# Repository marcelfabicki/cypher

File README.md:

<p align="center"><sub><i>Assembled Prototype v0.1.0</i></sub></p>

<h1 style="text-align:center;">CYPHER</h1>

**CYPHER** is an open-source, autonomous two-wheeled bipedal AI robot. Being a wheeled-legged robot, powered by a Raspberry Pi 5 and equipped with a camera and distance sensor, Cypher can navigate around obstacles and maintain balance on uneven surfaces, but most notably, through OpenAI's Realtime API and inspired by the personality of Tars (Interstellar), Cypher can talk, ask questions, and act on commands (with its own unique personality and humour).

## Project Status & Next Steps

The robot has been fully designed, printed and assembled. All hardware required for self-balancing and movement including servos, wheel BLDC motors and encoders, buck converters, and ultrasonic distance sensor have been installed and connected to the PCB so the next stage is to begin coding leg-movement and self-balancing firmware on the ESP32.

Some modifications had to be made to the PCB. These included soldering wires to the underside corresponding to pins 5, 15, 21, and 22 of the ESP32 to allow for I2C communication with the AS5600 magnetic encoders - originally PCB routed to PWM input pins which unfortunately proved unreliable. In addition 2.2k pull-up resisters were soldered to pins 5 and 15 to stabilise the I2C line. In v1 the PCB files ([hardware/pcb/](hardware/pcb/)) will be re-routed according to any modification.

The current design (available inside [hardware/cad](hardware/cad/)) includes approximately 45 3d-printed parts and over 130 screws to assemble. The BOM, full assembly instructions and documentation will be available with v1. 

## Hardware Overview
- **Battery:** 11.1V 3S 2200mAh LiPo
- **PCB:** 2 layer custom PCB for power distribution & signal routing
- **Compute:** ESP32 + Raspberry Pi 5
- **Sensors:** AS5600 magnetic encoders, INA226 voltage sensor, MPU6050 IMU, INMP441 microphone, HCSR04 ultrasonic distance sensor
- **BLDC Driver:** SimpleFOCMini driver
- **Actuators:** MG996R + 20kg servos, 2208 80T brushless gimbal motors
- **Buck-Converters:** XL4016, 60W DFRobot Adjustable Buck Module

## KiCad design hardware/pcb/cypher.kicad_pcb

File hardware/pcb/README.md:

# PCB Hardware Status

## Rev 0.1 (Current - Requires Modification)
- Functional with manual modifications (soldering additional wires and pull-up resistors to the underside ESP32 pins)
- Gerbers will be included once changes for Rev 0.2 have been made

## Planned for Rev 0.2
- Re-route AS5600 magnetic encoder connector traces with ESP32
- Add 2.2k I2C pull-ups

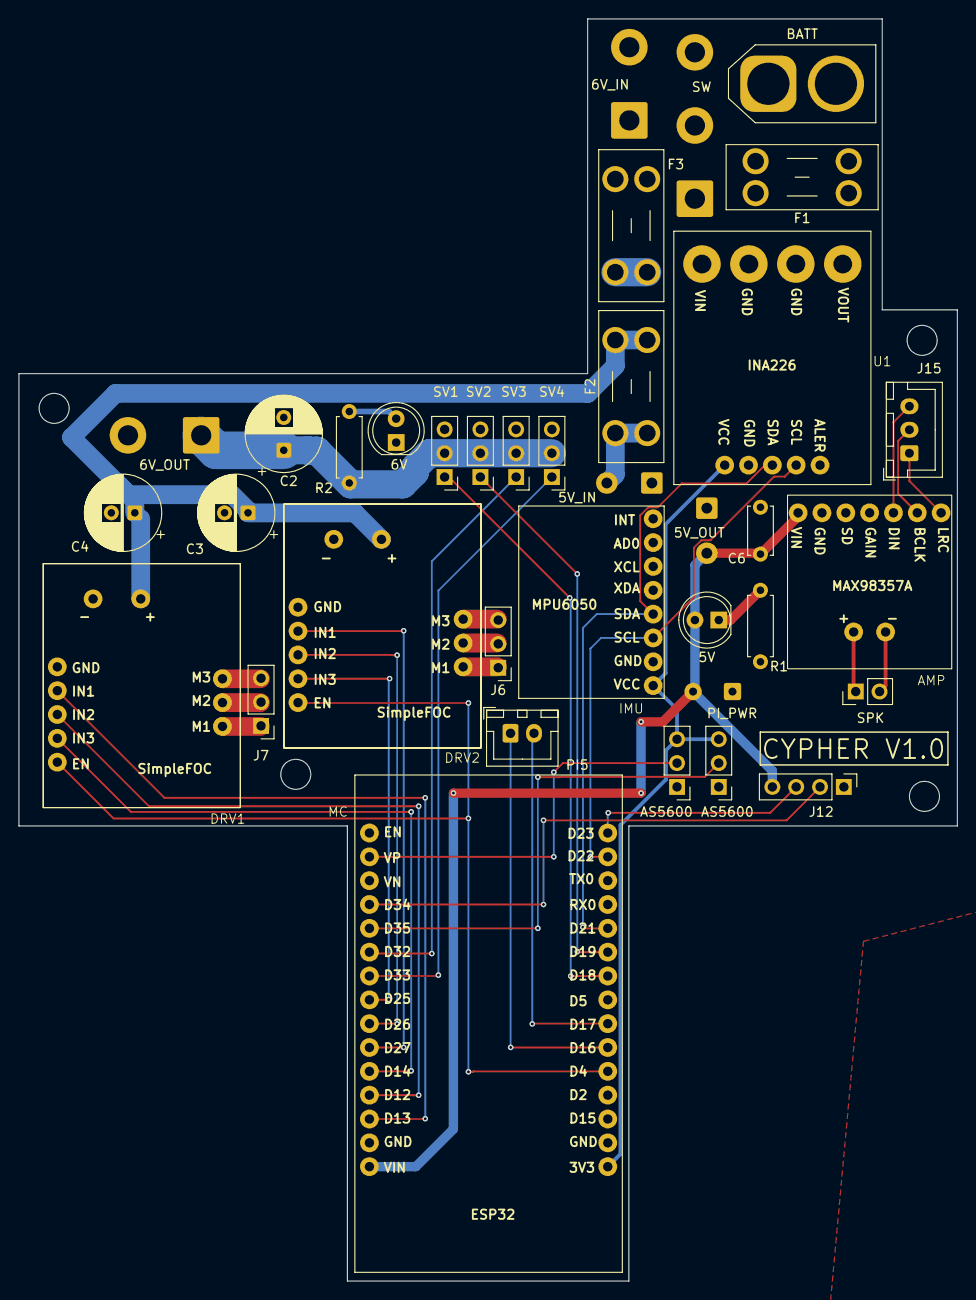
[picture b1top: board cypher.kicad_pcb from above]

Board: 2 copper layers, 100.0 x 134.5 mm, 36 parts (0 on the bottom side), 42 nets.

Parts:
5V, 6V: LED; LED_D5.0mm
5V_IN: UBEC IN; SolderWire-0.5sqmm_1x02_P4.8mm_D0.9mm_OD2.3mm
5V_OUT: UBEC OUT; SolderWire-0.5sqmm_1x02_P4.8mm_D0.9mm_OD2.3mm
6V_IN: XL4016 IN; SolderWire-1.5sqmm_1x02_P7.8mm_D1.7mm_OD3.9mm
6V_OUT: XL4016 OUT; SolderWire-1.5sqmm_1x02_P7.8mm_D1.7mm_OD3.9mm
AMP: MAX98357A Amplifer; MAX98357A Module
AS5600, AS5600#2: AS5600; PinHeader_1x03_P2.54mm_Vertical
BATT: BATT IN; AMASS_XT60-F_1x02_P7.20mm_Vertical
C2: C_Polarized; CP_Radial_D8.0mm_P3.50mm
C3, C4: C_Polarized; CP_Radial_D8.0mm_P2.50mm
C6: C; C_Disc_D5.0mm_W2.5mm_P5.00mm
DRV1, DRV2: SimpleFOC
F1, F2, F3: Fuse; Fuseholder_Blade_Mini_Keystone_3568
IMU: MPU6050 IMU; MPU6050 Module
J6, J7: Motor; PinHeader_1x03_P2.54mm_Vertical
J12: HCSRO4P; PinHeader_1x04_P2.54mm_Vertical
J15: PI Audio; JST_XH_B3B-XH-A_1x03_P2.50mm_Vertical
MC: ESP32; ESP32 Module
PI5: PI Communication; JST_XH_B2B-XH-A_1x02_P2.50mm_Vertical
PI_PWR: PI Power; SolderWire-0.25sqmm_1x02_P4.2mm_D0.65mm_OD1.7mm
R1, R2: 330; R_Axial_DIN0207_L6.3mm_D2.5mm_P7.62mm_Horizontal
SPK: Speaker; PinHeader_1x02_P2.54mm_Vertical
SV1: Servo4; PinHeader_1x03_P2.54mm_Vertical
SV2: Servo3; PinHeader_1x03_P2.54mm_Vertical
SV3: Servo2; PinHeader_1x03_P2.54mm_Vertical
SV4: Servo1; PinHeader_1x03_P2.54mm_Vertical
SW: Switch; SolderWire-1.5sqmm_1x03_P7.8mm_D1.7mm_OD3.9mm
U1: INA226; INA226 Module

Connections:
12V_SW: SW.1, U1.4 (VIN)
12V_SYS: C3.1, C4.1, DRV1.7 (+), DRV2.7 (+), F2.2, F3.1, U1.1 (VOUT)
+3V3: AS5600.3, AS5600#2.3, IMU.1 (VCC), MC.16 (3V3), U1.9 (VCC)
+5V: 5V.2 (A), 5V_OUT.2, AMP.9 (VIN), C6.2, J12.4, MC.1 (VIN), PI_PWR.2
+6V_DIRTY: 6V_OUT.1, C2.1, R2.1, SV1.2, SV2.2, SV3.2, SV4.2
+12V: BATT.2, F1.1
GND: 5V_IN.1, 5V_OUT.1, 6V.1 (K), 6V_IN.2, 6V_OUT.2, AMP.6 (GAIN), AMP.8 (GND), AS5600.1, AS5600#2.1, BATT.1, C2.2, C3.2, C4.2, C6.1, DRV1.1 (GND), DRV1.6 (-), DRV2.1 (GND), DRV2.6 (-), IMU.2 (GND), J12.1, MC.2 (GND), PI_PWR.1, R1.2, SV1.3, SV2.3, SV3.3, SV4.3, SW.3, U1.2 (GND), U1.3 (GND), U1.8 (GND)
unnamed: 5V.1 (K), R1.1
unnamed: 6V.2 (A), R2.2
unnamed: F1.2, SW.2
unnamed: 6V_IN.1, F3.2
unnamed: DRV2.10 (M1), J6.1
unnamed: DRV2.9 (M2), J6.2
unnamed: DRV2.8 (M3), J6.3
unnamed: DRV1.10 (M1), J7.1
unnamed: DRV1.9 (M2), J7.2
unnamed: DRV1.8 (M3), J7.3
unnamed: MC.9 (D33), SV4.1
unnamed: MC.10 (D32), SV3.1
unnamed: MC.25 (D19), SV2.1
unnamed: MC.24 (D18), SV1.1
unnamed: J12.2, MC.12 (D34)
unnamed: J12.3, MC.30 (D23)
unnamed: AMP.2 (+), SPK.1
unnamed: AMP.1 (-), SPK.2
unnamed: MC.21 (D16), PI5.1
unnamed: MC.22 (D17), PI5.2
unnamed: AMP.3 (LRC), J15.1
unnamed: AMP.4 (BCLK), J15.2
unnamed: AMP.5 (DIN), J15.3
unnamed: AS5600#2.2, MC.14 (VP)
unnamed: AS5600.2, MC.11 (D35)
unnamed: 5V_IN.2, F2.1
unnamed: IMU.3 (SCL), MC.29 (D22), U1.6 (SCL)
unnamed: IMU.4 (SDA), MC.26 (D21), U1.7 (SDA)
unnamed: DRV1.5 (EN), DRV2.5 (EN), MC.20 (D4)
unnamed: DRV2.2 (IN1), MC.6 (D27)
unnamed: DRV2.3 (IN2), MC.7 (D26)
unnamed: DRV2.4 (IN3), MC.8 (D25)
unnamed: DRV1.2 (IN1), MC.3 (D13)
unnamed: DRV1.3 (IN2), MC.4 (D12)
unnamed: DRV1.4 (IN3), MC.5 (D14)
